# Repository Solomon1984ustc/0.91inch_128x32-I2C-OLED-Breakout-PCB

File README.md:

# 0.91inch_128x32-I2C-OLED-Breakout-PCB

### PCB

## Schematic

## B.O.M

 please see bom/ibom.html

## Oled

[0.91inch 128x32 oled ch1115 （compatible ssd1306）](https://item.taobao.com/item.htm?id=608788330960)

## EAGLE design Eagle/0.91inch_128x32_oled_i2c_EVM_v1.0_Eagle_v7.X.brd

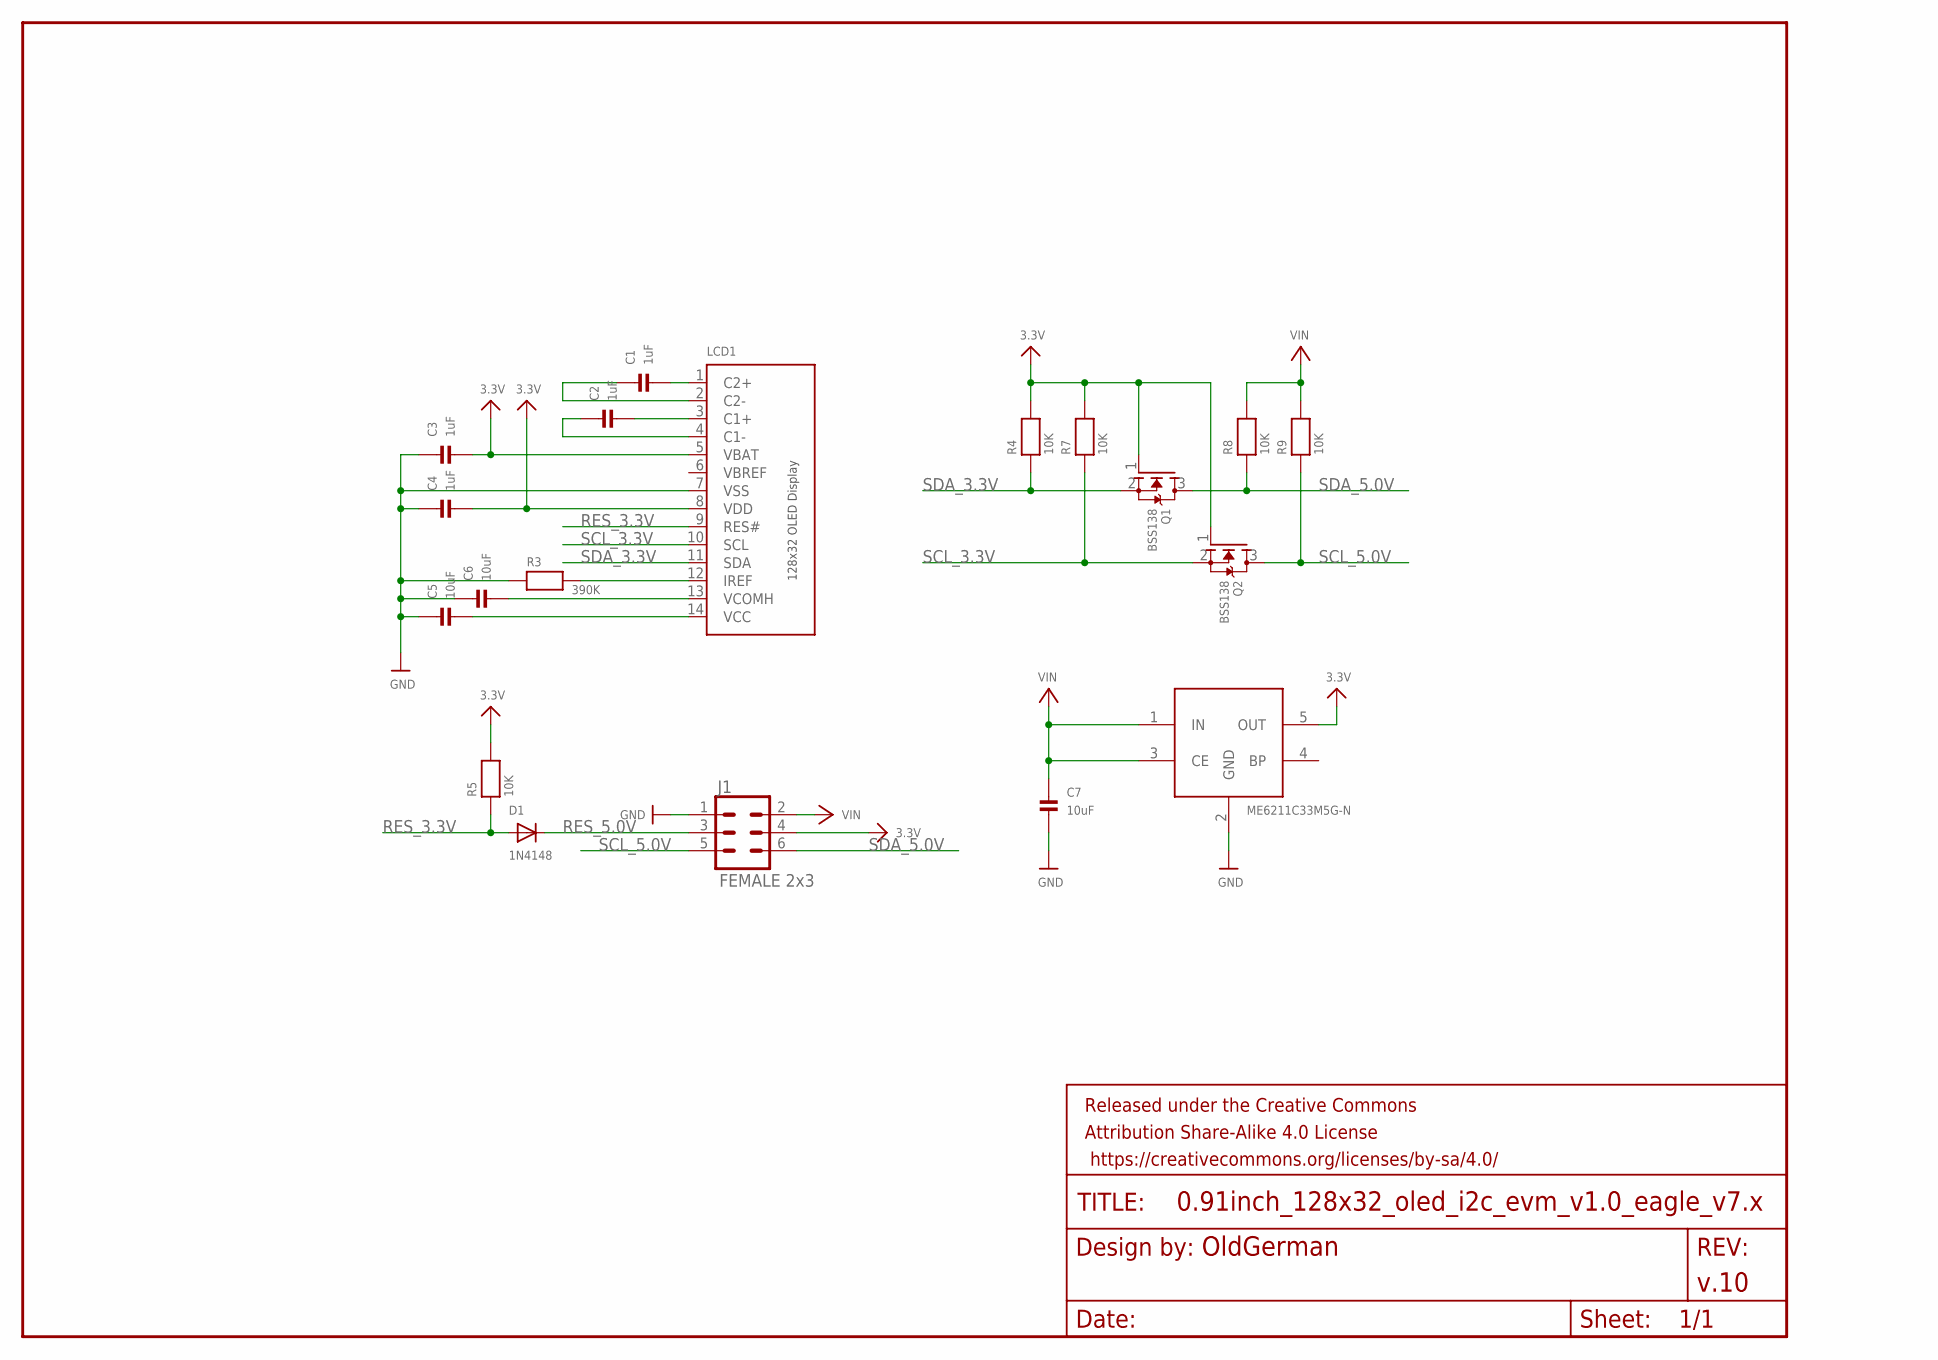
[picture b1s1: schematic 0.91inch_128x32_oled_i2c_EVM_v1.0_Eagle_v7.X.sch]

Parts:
C1, C2, C3, C4: 1uF; 0603
C5, C6, C7: 10uF; 0603
D1: 1N4148; SOD-323F
FRAME2: FRAME-LETTER; CREATIVE_COMMONS
J1: FEMALE 2x3; 2X3
LCD1: 0.91INCH_OLED_128X32_CH1115; 0.91INCH_128X32_OLED_CH1115
Q1, Q2: BSS138; SOT23-WIDE
R3: 390K; 0603
R4, R5, R7, R8, R9: 10K; 0603
U$6: ME6211C33M5G-N; SOT23-5

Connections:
3.3V: C3.2, J1.4, LCD1.5 (VBAT), Q1.1 (G), Q2.1 (G), R4.2, R5.2, R7.2, U$6.5 (OUT)
GND: C3.1, C4.1, C5.1, C6.1, C7.2, J1.1, LCD1.7 (VSS), R3.1, U$6.2 (GND)
unnamed: C1.2, LCD1.1 (C2+)
unnamed: C1.1, LCD1.2 (C2-)
unnamed: C2.2, LCD1.3 (C1+)
unnamed: C2.1, LCD1.4 (C1-)
unnamed: C6.2, LCD1.13 (VCOMH)
unnamed: C5.2, LCD1.14 (VCC)
unnamed: LCD1.12 (IREF), R3.2
unnamed: C4.2, LCD1.8 (VDD)
RES_3.3V: D1.A, LCD1.9 (RES#), R5.1
RES_5.0V: D1.C, J1.3
SCL_3.3V: LCD1.10 (SCL), Q2.2 (S), R7.1
SCL_5.0V: J1.5, Q2.3 (D), R9.1
SDA_3.3V: LCD1.11 (SDA), Q1.2 (S), R4.1
SDA_5.0V: J1.6, Q1.3 (D), R8.1
VBREF: LCD1.6 (VBREF)
VIN: C7.1, J1.2, R8.2, R9.2, U$6.1 (IN), U$6.3 (CE)

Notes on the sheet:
OldGerman
v.10

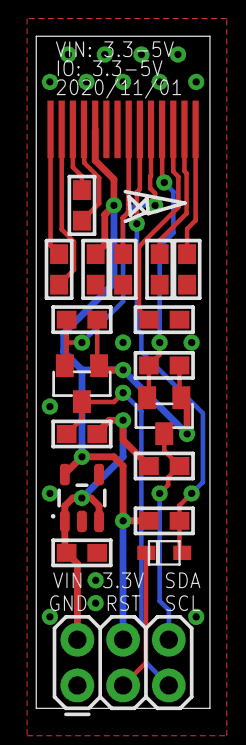
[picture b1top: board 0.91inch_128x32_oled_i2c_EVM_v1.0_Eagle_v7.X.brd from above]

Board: 2 copper layers, 9.7 x 37.3 mm, 20 parts (1 on the bottom side), 17 nets.

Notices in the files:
parts and their libraries:
SparkFun-IC-Power: Licensing: Creative Commons ShareAlike 4.0 International - https://creativecommons.org/licenses/by-sa/4.0
SparkFun-Aesthetics: Released under the Creative Commons Attribution Share-Alike 4.0 License
SparkFun-Aesthetics: https://creativecommons.org/licenses/by-sa/4.0
